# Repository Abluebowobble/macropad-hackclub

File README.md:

# Kittypad
This is a macropad to add macros on :) i'll probably add shortcuts to open apps like git and terminal, and maybe some shortcuts to fill out git commands if I can figure out an efficient way to do it.

# CAD
Image of the CAD for this project!

The heatset inserts would be placed in all the holds to keep the case together and keep the pcb board in place!
I have items poking out both the front side and the backside, so I'll need to be careful about that when assembling the entire thing. I'll also look into creating adding depressiosn for all the diodes and the XIAO, but thats for later.

# PCB and Schematic
Heres an image of the PCB board and schematic!

Image of the pcb

Image of schematic

# BOM
Here's everything I probably need
- 15x MX-Style switches
- 15x DSA Keycaps
- 7x M3x5mx4mm heatset inserts
- 7x M3x16mm SHCS Bolts
- 16x 1N4148 Diodes
- 16x SK6812 MINI-E LEDs
- 1x 0.91" 128x32 OLED Display
- 1x EC11 Rotary Encoder
- 1x XIAO RP2040
- 1x Case (2 printed parts)

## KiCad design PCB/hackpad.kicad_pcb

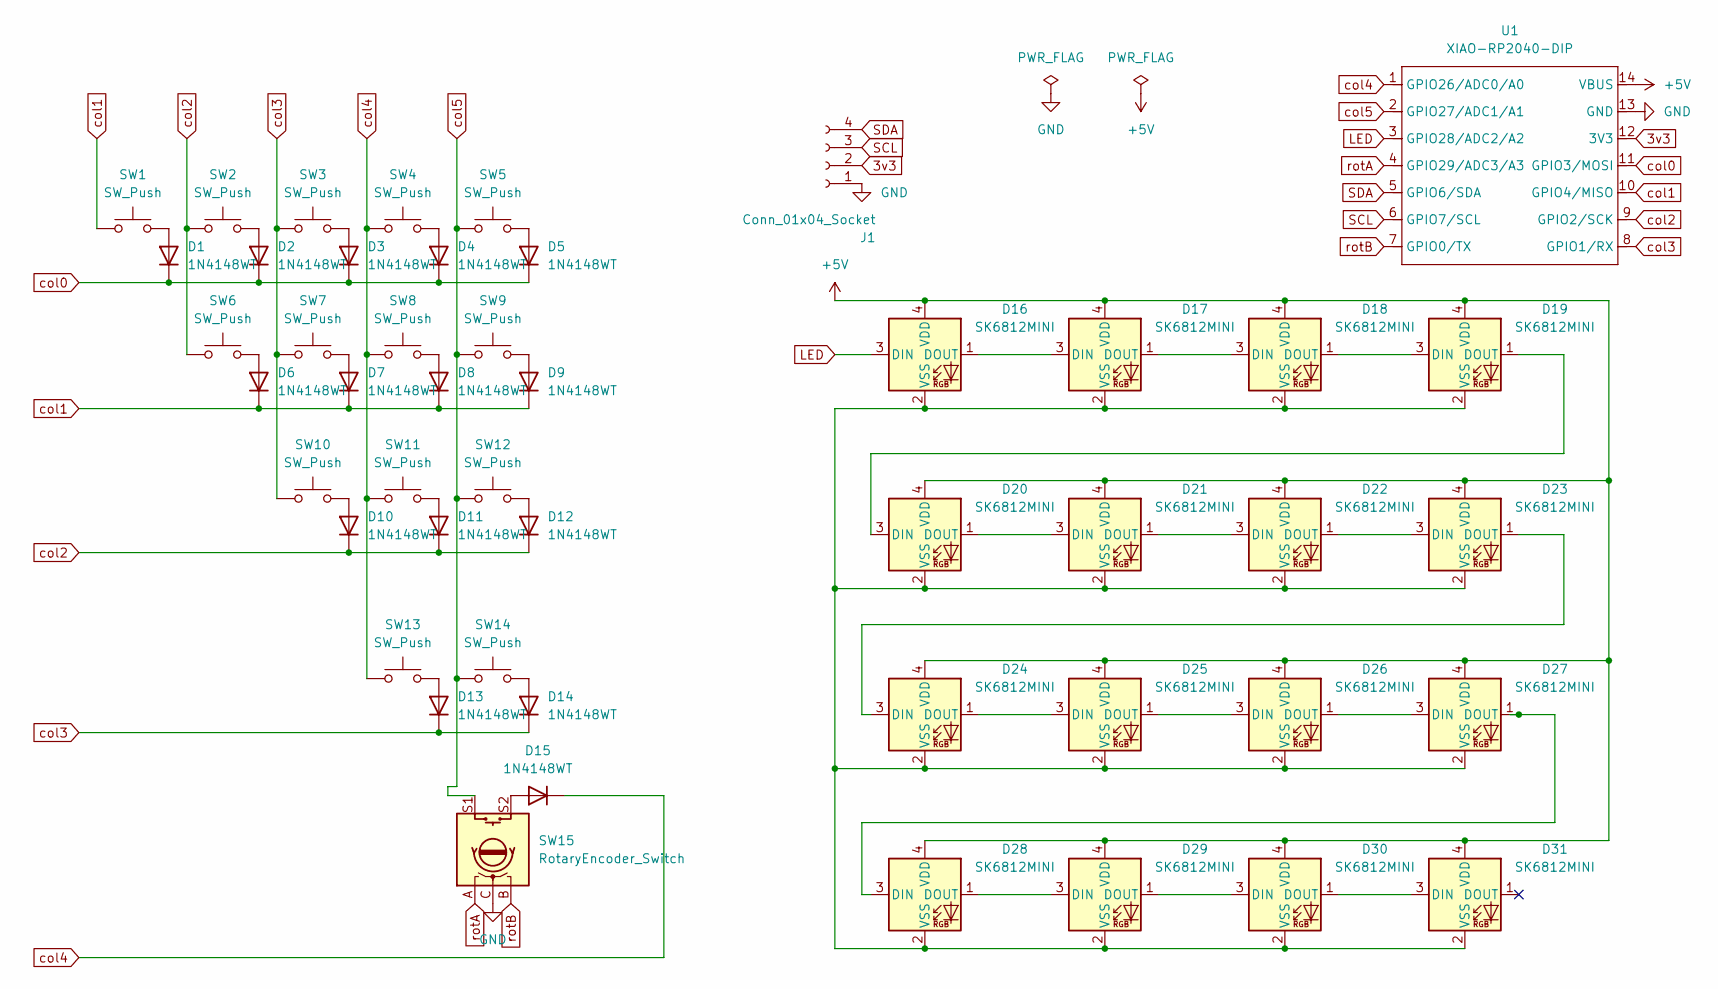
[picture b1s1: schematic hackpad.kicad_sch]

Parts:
D1, D2, D3, D4, D5, D6, D7, D8, D9, D10, D11, D12, D13, D14, D15: 1N4148WT; D_A-405_P10.16mm_Horizontal
D16, D17, D18, D19, D20, D21, D22, D23, D24, D25, D26, D27, D28, D29, D30, D31: SK6812MINI; SK6812-MINI-E
J1: Conn_01x04_Socket; SSD1306-0.91-OLED-4pin-128x32
SW1, SW2, SW3, SW4, SW5, SW6, SW7, SW8, SW9, SW10, SW11, SW12, SW13, SW14: SW_Push; SW_Cherry_MX_1.00u_PCB
SW15: RotaryEncoder_Switch; RotaryEncoder_Alps_EC11E-Switch_Vertical_H20mm
U1: XIAO-RP2040-DIP

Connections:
3v3: J1.2, U1.12 (3V3)
+5V: D16.4 (VDD), D17.4 (VDD), D18.4 (VDD), D19.4 (VDD), D20.4 (VDD), D21.4 (VDD), D22.4 (VDD), D23.4 (VDD), D24.4 (VDD), D25.4 (VDD), D26.4 (VDD), D27.4 (VDD), D28.4 (VDD), D29.4 (VDD), D30.4 (VDD), D31.4 (VDD), U1.14 (VBUS)
GND: J1.1, SW15.C, U1.13 (GND)
LED: D16.3 (DIN), U1.3 (GPIO28/ADC2/A2)
unnamed: D1.2 (A), SW1.2
unnamed: D2.2 (A), SW2.2
unnamed: D3.2 (A), SW3.2
unnamed: D4.2 (A), SW4.2
unnamed: D5.2 (A), SW5.2
unnamed: D6.2 (A), SW6.2
unnamed: D7.2 (A), SW7.2
unnamed: D8.2 (A), SW8.2
unnamed: D9.2 (A), SW9.2
unnamed: D10.2 (A), SW10.2
unnamed: D11.2 (A), SW11.2
unnamed: D12.2 (A), SW12.2
unnamed: D13.2 (A), SW13.2
unnamed: D14.2 (A), SW14.2
unnamed: D15.2 (A), SW15.S2
unnamed: D16.1 (DOUT), D17.3 (DIN)
unnamed: D16.2 (VSS), D17.2 (VSS), D18.2 (VSS), D19.2 (VSS), D20.2 (VSS), D21.2 (VSS), D22.2 (VSS), D23.2 (VSS), D24.2 (VSS), D25.2 (VSS), D26.2 (VSS), D27.2 (VSS), D28.2 (VSS), D29.2 (VSS), D30.2 (VSS), D31.2 (VSS)
unnamed: D17.1 (DOUT), D18.3 (DIN)
unnamed: D18.1 (DOUT), D19.3 (DIN)
unnamed: D19.1 (DOUT), D20.3 (DIN)
unnamed: D20.1 (DOUT), D21.3 (DIN)
unnamed: D21.1 (DOUT), D22.3 (DIN)
unnamed: D22.1 (DOUT), D23.3 (DIN)
unnamed: D23.1 (DOUT), D24.3 (DIN)
unnamed: D24.1 (DOUT), D25.3 (DIN)
unnamed: D25.1 (DOUT), D26.3 (DIN)
unnamed: D26.1 (DOUT), D27.3 (DIN)
unnamed: D27.1 (DOUT), D28.3 (DIN)
unnamed: D28.1 (DOUT), D29.3 (DIN)
unnamed: D29.1 (DOUT), D30.3 (DIN)
unnamed: D30.1 (DOUT), D31.3 (DIN)
SCL: J1.3, U1.6 (GPIO7/SCL)
SDA: J1.4, U1.5 (GPIO6/SDA)
col0: D1.1 (K), D2.1 (K), D3.1 (K), D4.1 (K), D5.1 (K), U1.11 (GPIO3/MOSI)
col1: D6.1 (K), D7.1 (K), D8.1 (K), D9.1 (K), SW1.1, U1.10 (GPIO4/MISO)
col2: D10.1 (K), D11.1 (K), D12.1 (K), SW2.1, SW6.1, U1.9 (GPIO2/SCK)
col3: D13.1 (K), D14.1 (K), SW3.1, SW7.1, SW10.1, U1.8 (GPIO1/RX)
col4: D15.1 (K), SW4.1, SW8.1, SW11.1, SW13.1, U1.1 (GPIO26/ADC0/A0)
col5: SW5.1, SW9.1, SW12.1, SW14.1, SW15.S1, U1.2 (GPIO27/ADC1/A1)
rotA: SW15.A, U1.4 (GPIO29/ADC3/A3)
rotB: SW15.B, U1.7 (GPIO0/TX)

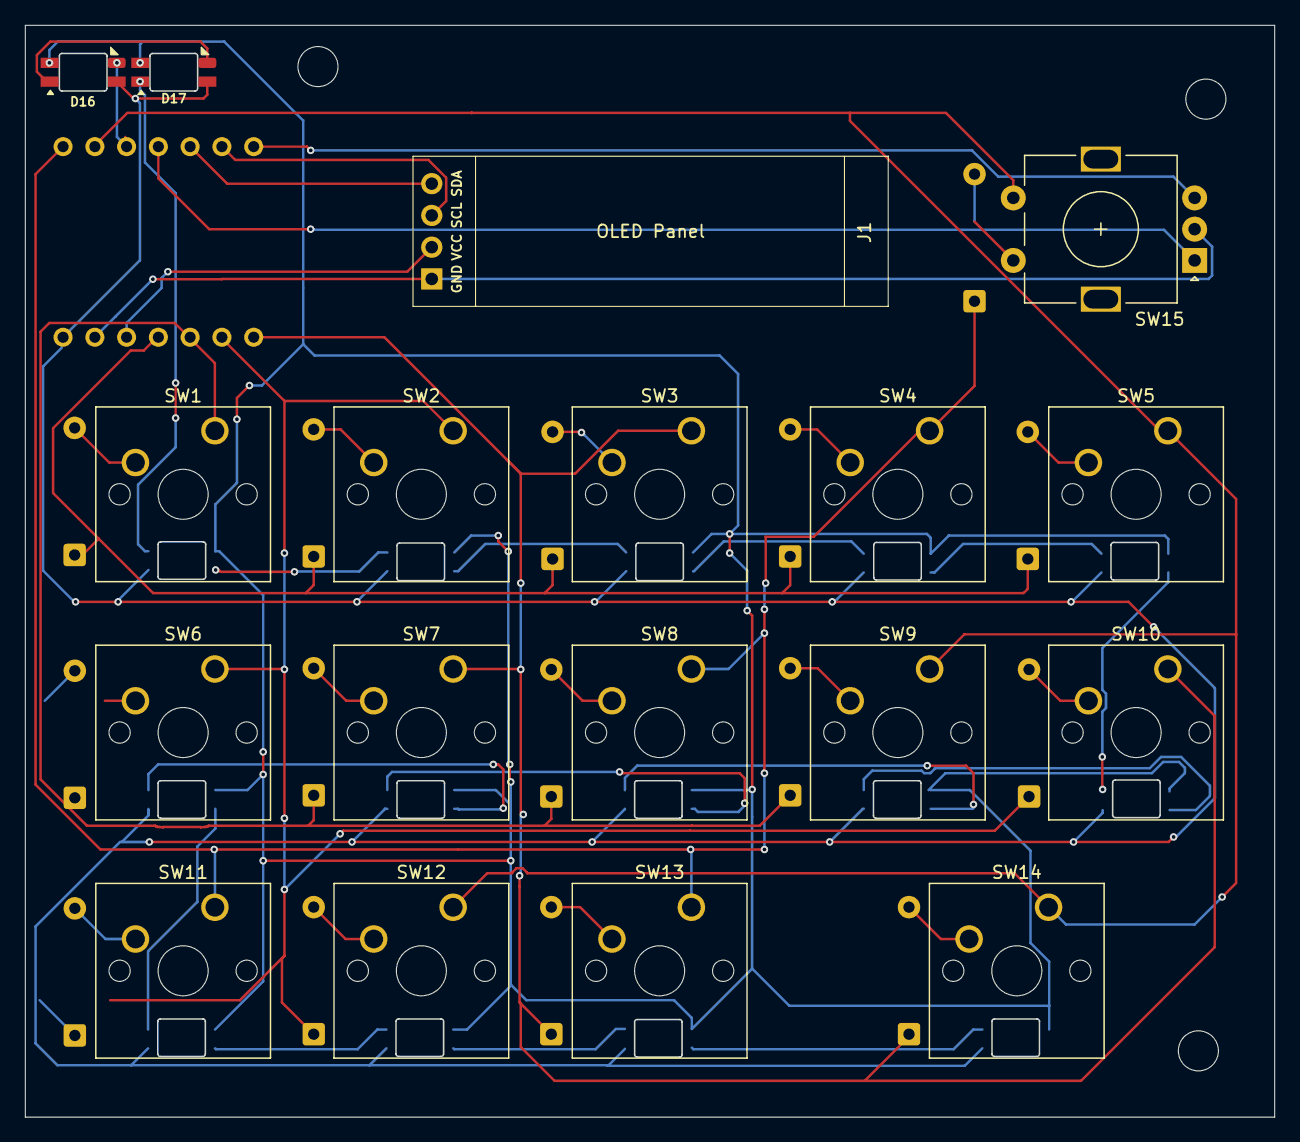
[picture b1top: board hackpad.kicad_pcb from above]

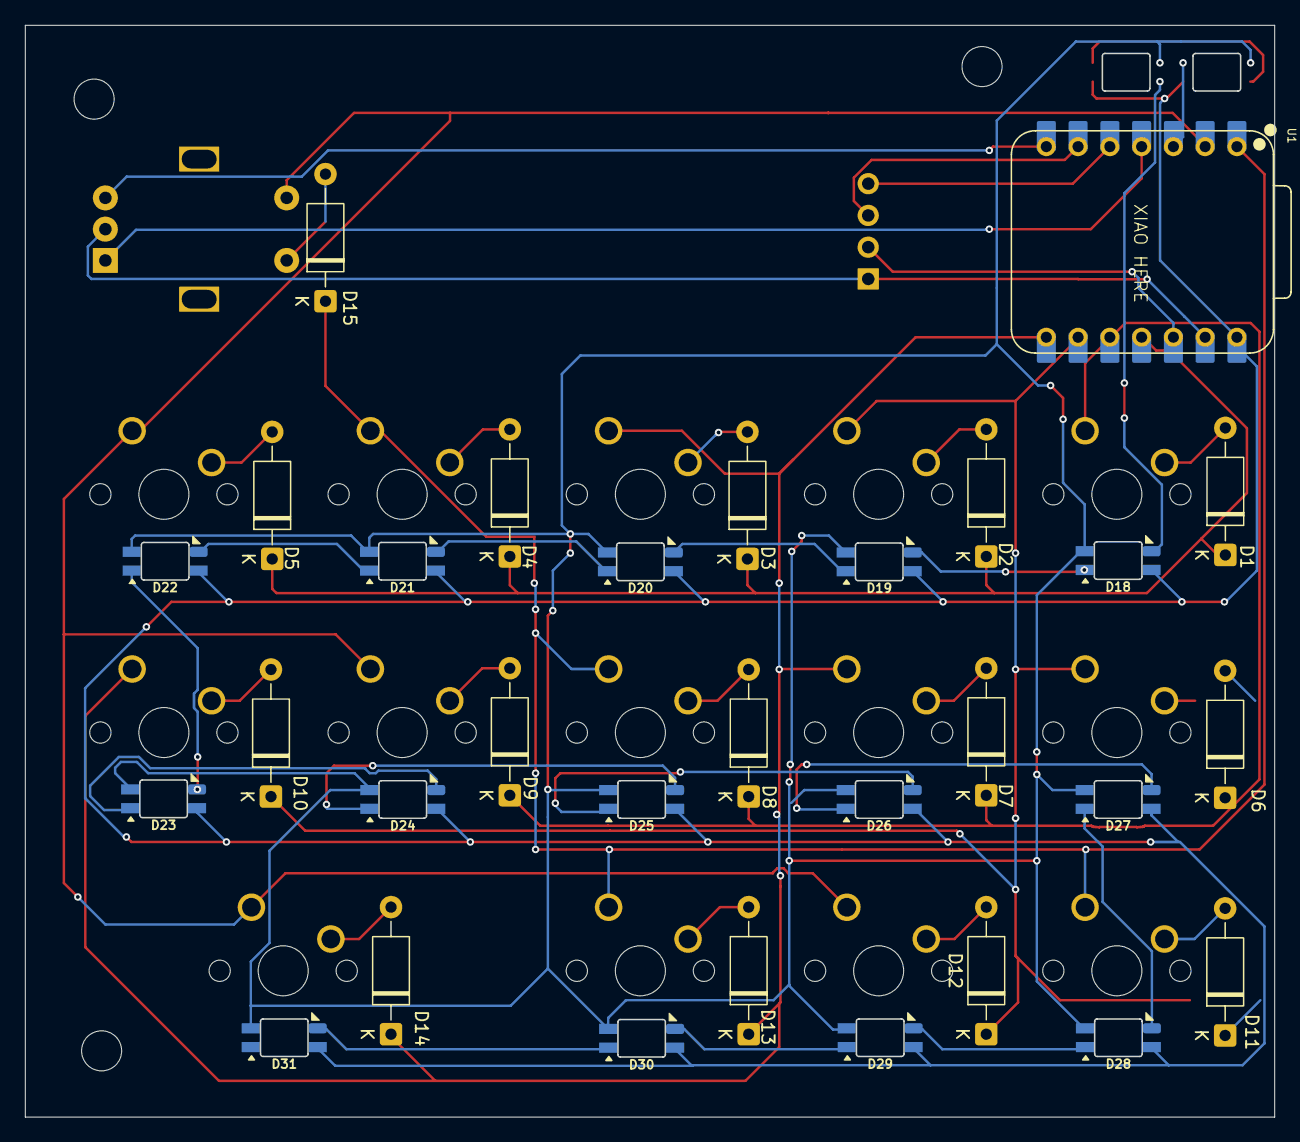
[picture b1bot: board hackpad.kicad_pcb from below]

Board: 2 copper layers, 99.8 x 87.2 mm, 48 parts (30 on the bottom side), 45 nets.

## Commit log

2025-12-31 changed cad file from stl to step
2025-12-31 Improve README formatting and add line breaks
    Fixed formatting and added line breaks in the README.
2025-12-31 Fix formatting and escape characters in README.md
    Corrected formatting and removed unnecessary escape characters in README.
